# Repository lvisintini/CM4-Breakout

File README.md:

# CM4-Breakout (project discontinued)

A simple 2 layer PCB board for the Raspberry pi CM4 designed on KiCad.

##  Objectives

- Ceate a PCB board with all the CM4 pins exposed so that it can be used for prototyping as part of a breadboard.
- Learn how to layout a board in KiCad
- Learn how to design for the CM4

## Outcomes and conclusions

While it was certainly educational to attempt to design this board, I wont be finishing this project.

There are many reasons, but the main problem is that it is just not very practical:
- Most projects wont need to use everything and creating a breakout board that only uses the required features is simpler.
- Exposing some pins as anything other that the ports/jacks they are designed for is nonsensical.
- There is already an [abundance](https://github.com/geerlingguy/raspberry-pi-pcie-devices) of open-hardware projects with desing breakout boards for the CM4. There is probably no need for a new one with a narrow use case such as this one..
- Trying to fit all the traces using only 2 layers is too much of a constraint (the CM4IO uses 4)

However, this was not a waste of time:
- Learned a lot about the CM4 module
- Learned a lot about KiCad 6 (pre-release nightly versions)
- Learned a lot about PCB design in general

## Screenshot

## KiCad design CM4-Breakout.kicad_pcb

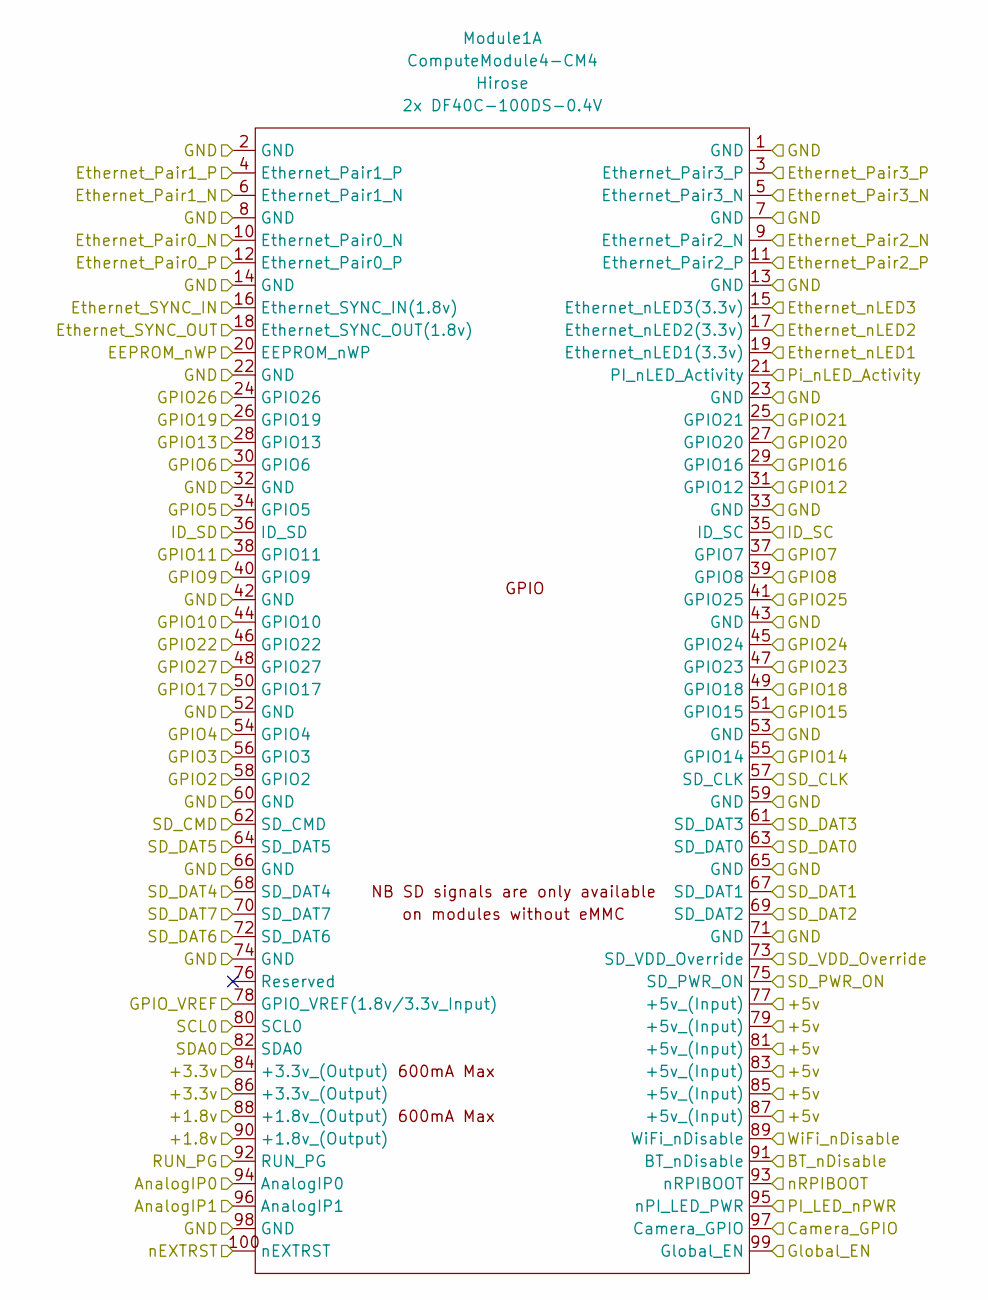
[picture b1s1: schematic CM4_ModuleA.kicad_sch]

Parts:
Module1: ComputeModule4-CM4; Raspberry-Pi-4-Compute-Module

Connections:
/+1.8v: Module1.88 (+1.8v_(Output)), Module1.90 (+1.8v_(Output)); also elsewhere on the board
/+3.3v: Module1.84 (+3.3v_(Output)), Module1.86 (+3.3v_(Output)); also elsewhere on the board
/+5v: Module1.77 (+5v_(Input)), Module1.79 (+5v_(Input)), Module1.81 (+5v_(Input)), Module1.83 (+5v_(Input)), Module1.85 (+5v_(Input)), Module1.87 (+5v_(Input)); also elsewhere on the board
/AnalogIP0: Module1.94 (AnalogIP0); also elsewhere on the board
/AnalogIP1: Module1.96 (AnalogIP1); also elsewhere on the board
/BT_nDisable: Module1.91 (BT_nDisable); also elsewhere on the board
/Camera_GPIO: Module1.97 (Camera_GPIO); also elsewhere on the board
/EEPROM_nWP: Module1.20 (EEPROM_nWP); also elsewhere on the board
/Ethernet_Pair0_N: Module1.10 (Ethernet_Pair0_N); also elsewhere on the board
/Ethernet_Pair0_P: Module1.12 (Ethernet_Pair0_P); also elsewhere on the board
/Ethernet_Pair1_N: Module1.6 (Ethernet_Pair1_N); also elsewhere on the board
/Ethernet_Pair1_P: Module1.4 (Ethernet_Pair1_P); also elsewhere on the board
/Ethernet_Pair2_N: Module1.9 (Ethernet_Pair2_N); also elsewhere on the board
/Ethernet_Pair2_P: Module1.11 (Ethernet_Pair2_P); also elsewhere on the board
/Ethernet_Pair3_N: Module1.5 (Ethernet_Pair3_N); also elsewhere on the board
/Ethernet_Pair3_P: Module1.3 (Ethernet_Pair3_P); also elsewhere on the board
/Ethernet_SYNC_IN: Module1.16 (Ethernet_SYNC_IN(1.8v)); also elsewhere on the board
/Ethernet_SYNC_OUT: Module1.18 (Ethernet_SYNC_OUT(1.8v)); also elsewhere on the board
/Ethernet_nLED1: Module1.19 (Ethernet_nLED1(3.3v)); also elsewhere on the board
/Ethernet_nLED2: Module1.17 (Ethernet_nLED2(3.3v)); also elsewhere on the board
/Ethernet_nLED3: Module1.15 (Ethernet_nLED3(3.3v)); also elsewhere on the board
/GND: Module1.1 (GND), Module1.2 (GND), Module1.7 (GND), Module1.8 (GND), Module1.13 (GND), Module1.14 (GND), Module1.22 (GND), Module1.23 (GND), Module1.32 (GND), Module1.33 (GND), Module1.42 (GND), Module1.43 (GND), Module1.52 (GND), Module1.53 (GND), Module1.59 (GND), Module1.60 (GND), Module1.65 (GND), Module1.66 (GND), Module1.71 (GND), Module1.74 (GND), Module1.98 (GND); also elsewhere on the board
/GPIO2: Module1.58 (GPIO2); also elsewhere on the board
/GPIO3: Module1.56 (GPIO3); also elsewhere on the board
/GPIO4: Module1.54 (GPIO4); also elsewhere on the board
/GPIO5: Module1.34 (GPIO5); also elsewhere on the board
/GPIO6: Module1.30 (GPIO6); also elsewhere on the board
/GPIO7: Module1.37 (GPIO7); also elsewhere on the board
/GPIO8: Module1.39 (GPIO8); also elsewhere on the board
/GPIO9: Module1.40 (GPIO9); also elsewhere on the board
/GPIO10: Module1.44 (GPIO10); also elsewhere on the board
/GPIO11: Module1.38 (GPIO11); also elsewhere on the board
/GPIO12: Module1.31 (GPIO12); also elsewhere on the board
/GPIO13: Module1.28 (GPIO13); also elsewhere on the board
/GPIO14: Module1.55 (GPIO14); also elsewhere on the board
/GPIO15: Module1.51 (GPIO15); also elsewhere on the board
/GPIO16: Module1.29 (GPIO16); also elsewhere on the board
/GPIO17: Module1.50 (GPIO17); also elsewhere on the board
/GPIO18: Module1.49 (GPIO18); also elsewhere on the board
/GPIO19: Module1.26 (GPIO19); also elsewhere on the board
/GPIO20: Module1.27 (GPIO20); also elsewhere on the board
/GPIO21: Module1.25 (GPIO21); also elsewhere on the board
/GPIO22: Module1.46 (GPIO22); also elsewhere on the board
/GPIO23: Module1.47 (GPIO23); also elsewhere on the board
/GPIO24: Module1.45 (GPIO24); also elsewhere on the board
/GPIO25: Module1.41 (GPIO25); also elsewhere on the board
/GPIO26: Module1.24 (GPIO26); also elsewhere on the board
/GPIO27: Module1.48 (GPIO27); also elsewhere on the board
/GPIO_VREF: Module1.78 (GPIO_VREF(1.8v/3.3v_Input)); also elsewhere on the board
/Global_EN: Module1.99 (Global_EN); also elsewhere on the board
/ID_SC: Module1.35 (ID_SC); also elsewhere on the board
/ID_SD: Module1.36 (ID_SD); also elsewhere on the board
/PI_LED_nPWR: Module1.95 (nPI_LED_PWR); also elsewhere on the board
/Pi_nLED_Activity: Module1.21 (PI_nLED_Activity); also elsewhere on the board
/RUN_PG: Module1.92 (RUN_PG); also elsewhere on the board
/SCL0: Module1.80 (SCL0); also elsewhere on the board
/SDA0: Module1.82 (SDA0); also elsewhere on the board
/SD_CLK: Module1.57 (SD_CLK); also elsewhere on the board
/SD_CMD: Module1.62 (SD_CMD); also elsewhere on the board
/SD_DAT0: Module1.63 (SD_DAT0); also elsewhere on the board
/SD_DAT1: Module1.67 (SD_DAT1); also elsewhere on the board
/SD_DAT2: Module1.69 (SD_DAT2); also elsewhere on the board
/SD_DAT3: Module1.61 (SD_DAT3); also elsewhere on the board
/SD_DAT4: Module1.68 (SD_DAT4); also elsewhere on the board
/SD_DAT5: Module1.64 (SD_DAT5); also elsewhere on the board
/SD_DAT6: Module1.72 (SD_DAT6); also elsewhere on the board
/SD_DAT7: Module1.70 (SD_DAT7); also elsewhere on the board
/SD_PWR_ON: Module1.75 (SD_PWR_ON); also elsewhere on the board
/SD_VDD_Override: Module1.73 (SD_VDD_Override); also elsewhere on the board
/WiFi_nDisable: Module1.89 (WiFi_nDisable); also elsewhere on the board
/nEXTRST: Module1.100 (nEXTRST); also elsewhere on the board
/nRPIBOOT: Module1.93 (nRPIBOOT); also elsewhere on the board
no_connect_143: Module1.76 (Reserved)

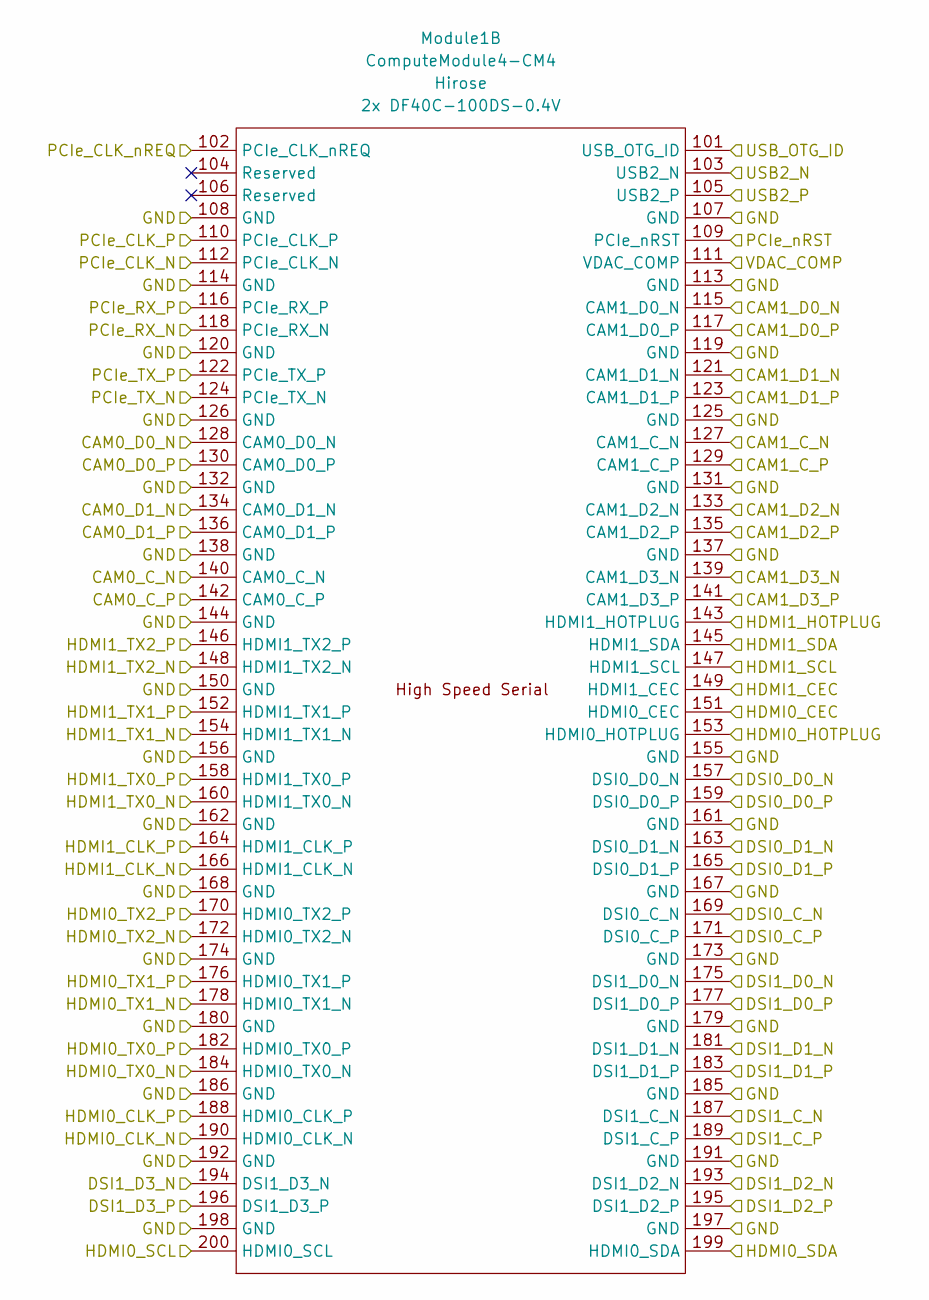
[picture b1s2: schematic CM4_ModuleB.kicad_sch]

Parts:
Module1: ComputeModule4-CM4; Raspberry-Pi-4-Compute-Module

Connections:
/CAM0_C_N: Module1.140 (CAM0_C_N); also elsewhere on the board
/CAM0_C_P: Module1.142 (CAM0_C_P); also elsewhere on the board
/CAM0_D0_N: Module1.128 (CAM0_D0_N); also elsewhere on the board
/CAM0_D0_P: Module1.130 (CAM0_D0_P); also elsewhere on the board
/CAM0_D1_N: Module1.134 (CAM0_D1_N); also elsewhere on the board
/CAM0_D1_P: Module1.136 (CAM0_D1_P); also elsewhere on the board
/CAM1_C_N: Module1.127 (CAM1_C_N); also elsewhere on the board
/CAM1_C_P: Module1.129 (CAM1_C_P); also elsewhere on the board
/CAM1_D0_N: Module1.115 (CAM1_D0_N); also elsewhere on the board
/CAM1_D0_P: Module1.117 (CAM1_D0_P); also elsewhere on the board
/CAM1_D1_N: Module1.121 (CAM1_D1_N); also elsewhere on the board
/CAM1_D1_P: Module1.123 (CAM1_D1_P); also elsewhere on the board
/CAM1_D2_N: Module1.133 (CAM1_D2_N); also elsewhere on the board
/CAM1_D2_P: Module1.135 (CAM1_D2_P); also elsewhere on the board
/CAM1_D3_N: Module1.139 (CAM1_D3_N); also elsewhere on the board
/CAM1_D3_P: Module1.141 (CAM1_D3_P); also elsewhere on the board
/DSI0_C_N: Module1.169 (DSI0_C_N); also elsewhere on the board
/DSI0_C_P: Module1.171 (DSI0_C_P); also elsewhere on the board
/DSI0_D0_N: Module1.157 (DSI0_D0_N); also elsewhere on the board
/DSI0_D0_P: Module1.159 (DSI0_D0_P); also elsewhere on the board
/DSI0_D1_N: Module1.163 (DSI0_D1_N); also elsewhere on the board
/DSI0_D1_P: Module1.165 (DSI0_D1_P); also elsewhere on the board
/DSI1_C_N: Module1.187 (DSI1_C_N); also elsewhere on the board
/DSI1_C_P: Module1.189 (DSI1_C_P); also elsewhere on the board
/DSI1_D0_N: Module1.175 (DSI1_D0_N); also elsewhere on the board
/DSI1_D0_P: Module1.177 (DSI1_D0_P); also elsewhere on the board
/DSI1_D1_N: Module1.181 (DSI1_D1_N); also elsewhere on the board
/DSI1_D1_P: Module1.183 (DSI1_D1_P); also elsewhere on the board
/DSI1_D2_N: Module1.193 (DSI1_D2_N); also elsewhere on the board
/DSI1_D2_P: Module1.195 (DSI1_D2_P); also elsewhere on the board
/DSI1_D3_N: Module1.194 (DSI1_D3_N); also elsewhere on the board
/DSI1_D3_P: Module1.196 (DSI1_D3_P); also elsewhere on the board
/GND: Module1.107 (GND), Module1.108 (GND), Module1.113 (GND), Module1.114 (GND), Module1.119 (GND), Module1.120 (GND), Module1.125 (GND), Module1.126 (GND), Module1.131 (GND), Module1.132 (GND), Module1.137 (GND), Module1.138 (GND), Module1.144 (GND), Module1.150 (GND), Module1.155 (GND), Module1.156 (GND), Module1.161 (GND), Module1.162 (GND), Module1.167 (GND), Module1.168 (GND), Module1.173 (GND), Module1.174 (GND), Module1.179 (GND), Module1.180 (GND), Module1.185 (GND), Module1.186 (GND), Module1.191 (GND), Module1.192 (GND), Module1.197 (GND), Module1.198 (GND); also elsewhere on the board
/HDMI0_CEC: Module1.151 (HDMI0_CEC); also elsewhere on the board
/HDMI0_CLK_N: Module1.190 (HDMI0_CLK_N); also elsewhere on the board
/HDMI0_CLK_P: Module1.188 (HDMI0_CLK_P); also elsewhere on the board
/HDMI0_HOTPLUG: Module1.153 (HDMI0_HOTPLUG); also elsewhere on the board
/HDMI0_SCL: Module1.200 (HDMI0_SCL); also elsewhere on the board
/HDMI0_SDA: Module1.199 (HDMI0_SDA); also elsewhere on the board
/HDMI0_TX0_N: Module1.184 (HDMI0_TX0_N); also elsewhere on the board
/HDMI0_TX0_P: Module1.182 (HDMI0_TX0_P); also elsewhere on the board
/HDMI0_TX1_N: Module1.178 (HDMI0_TX1_N); also elsewhere on the board
/HDMI0_TX1_P: Module1.176 (HDMI0_TX1_P); also elsewhere on the board
/HDMI0_TX2_N: Module1.172 (HDMI0_TX2_N); also elsewhere on the board
/HDMI0_TX2_P: Module1.170 (HDMI0_TX2_P); also elsewhere on the board
/HDMI1_CEC: Module1.149 (HDMI1_CEC); also elsewhere on the board
/HDMI1_CLK_N: Module1.166 (HDMI1_CLK_N); also elsewhere on the board
/HDMI1_CLK_P: Module1.164 (HDMI1_CLK_P); also elsewhere on the board
/HDMI1_HOTPLUG: Module1.143 (HDMI1_HOTPLUG); also elsewhere on the board
/HDMI1_SCL: Module1.147 (HDMI1_SCL); also elsewhere on the board
/HDMI1_SDA: Module1.145 (HDMI1_SDA); also elsewhere on the board
/HDMI1_TX0_N: Module1.160 (HDMI1_TX0_N); also elsewhere on the board
/HDMI1_TX0_P: Module1.158 (HDMI1_TX0_P); also elsewhere on the board
/HDMI1_TX1_N: Module1.154 (HDMI1_TX1_N); also elsewhere on the board
/HDMI1_TX1_P: Module1.152 (HDMI1_TX1_P); also elsewhere on the board
/HDMI1_TX2_N: Module1.148 (HDMI1_TX2_N); also elsewhere on the board
/HDMI1_TX2_P: Module1.146 (HDMI1_TX2_P); also elsewhere on the board
/PCIe_CLK_N: Module1.112 (PCIe_CLK_N); also elsewhere on the board
/PCIe_CLK_P: Module1.110 (PCIe_CLK_P); also elsewhere on the board
/PCIe_CLK_nREQ: Module1.102 (PCIe_CLK_nREQ); also elsewhere on the board
/PCIe_RX_N: Module1.118 (PCIe_RX_N); also elsewhere on the board
/PCIe_RX_P: Module1.116 (PCIe_RX_P); also elsewhere on the board
/PCIe_TX_N: Module1.124 (PCIe_TX_N); also elsewhere on the board
/PCIe_TX_P: Module1.122 (PCIe_TX_P); also elsewhere on the board
/PCIe_nRST: Module1.109 (PCIe_nRST); also elsewhere on the board
/USB2_N: Module1.103 (USB2_N); also elsewhere on the board
/USB2_P: Module1.105 (USB2_P); also elsewhere on the board
/USB_OTG_ID: Module1.101 (USB_OTG_ID); also elsewhere on the board
/VDAC_COMP: Module1.111 (VDAC_COMP); also elsewhere on the board
no_connect_141: Module1.104 (Reserved)
no_connect_142: Module1.106 (Reserved)

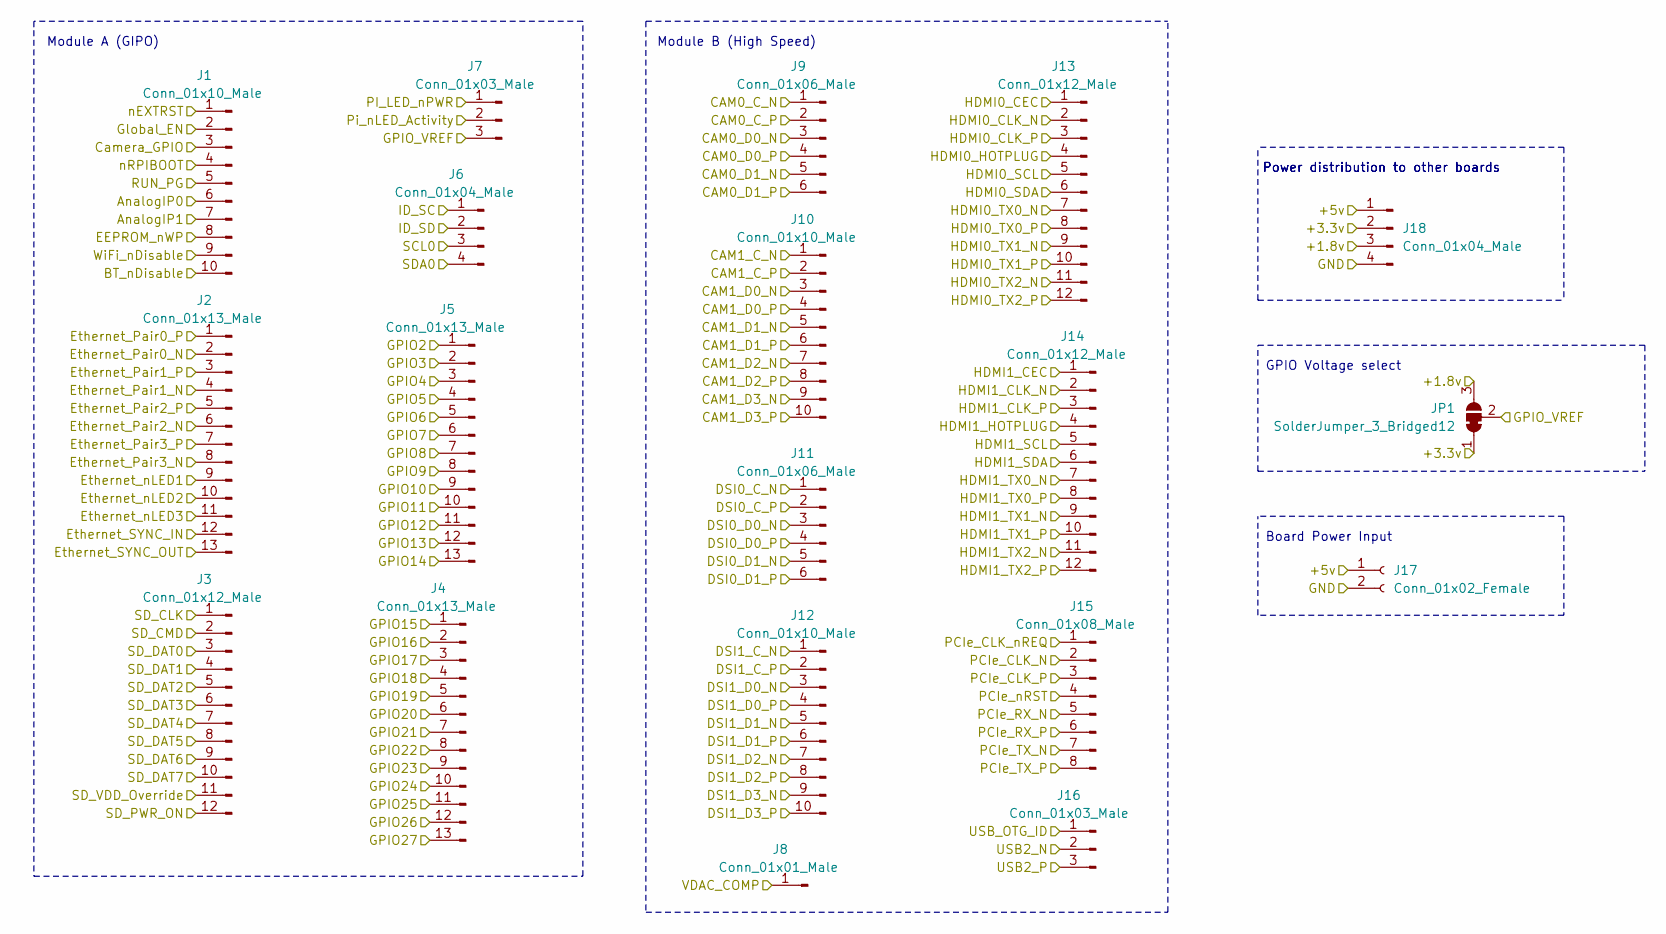
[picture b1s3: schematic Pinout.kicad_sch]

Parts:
J1, J10, J12: Conn_01x10_Male; PinHeader_1x10_P2.54mm_Vertical
J2, J4, J5: Conn_01x13_Male; PinHeader_1x13_P2.54mm_Vertical
J3, J13, J14: Conn_01x12_Male; PinHeader_1x12_P2.54mm_Vertical
J6, J18: Conn_01x04_Male; PinHeader_1x04_P2.54mm_Vertical
J7, J16: Conn_01x03_Male; PinHeader_1x03_P2.54mm_Vertical
J8: Conn_01x01_Male; PinHeader_1x01_P2.54mm_Vertical
J9, J11: Conn_01x06_Male; PinHeader_1x06_P2.54mm_Vertical
J15: Conn_01x08_Male; PinHeader_1x08_P2.54mm_Vertical
J17: Conn_01x02_Female; PinHeader_1x02_P2.54mm_Vertical
JP1: SolderJumper_3_Bridged12; SolderJumper-3_P1.3mm_Bridged12_RoundedPad1.0x1.5mm

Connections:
/+1.8v: J18.3, JP1.3 (B); also elsewhere on the board
/+3.3v: J18.2, JP1.1 (A); also elsewhere on the board
/+5v: J17.1, J18.1; also elsewhere on the board
/AnalogIP0: J1.6; also elsewhere on the board
/AnalogIP1: J1.7; also elsewhere on the board
/BT_nDisable: J1.10; also elsewhere on the board
/CAM0_C_N: J9.1; also elsewhere on the board
/CAM0_C_P: J9.2; also elsewhere on the board
/CAM0_D0_N: J9.3; also elsewhere on the board
/CAM0_D0_P: J9.4; also elsewhere on the board
/CAM0_D1_N: J9.5; also elsewhere on the board
/CAM0_D1_P: J9.6; also elsewhere on the board
/CAM1_C_N: J10.1; also elsewhere on the board
/CAM1_C_P: J10.2; also elsewhere on the board
/CAM1_D0_N: J10.3; also elsewhere on the board
/CAM1_D0_P: J10.4; also elsewhere on the board
/CAM1_D1_N: J10.5; also elsewhere on the board
/CAM1_D1_P: J10.6; also elsewhere on the board
/CAM1_D2_N: J10.7; also elsewhere on the board
/CAM1_D2_P: J10.8; also elsewhere on the board
/CAM1_D3_N: J10.9; also elsewhere on the board
/CAM1_D3_P: J10.10; also elsewhere on the board
/Camera_GPIO: J1.3; also elsewhere on the board
/DSI0_C_N: J11.1; also elsewhere on the board
/DSI0_C_P: J11.2; also elsewhere on the board
/DSI0_D0_N: J11.3; also elsewhere on the board
/DSI0_D0_P: J11.4; also elsewhere on the board
/DSI0_D1_N: J11.5; also elsewhere on the board
/DSI0_D1_P: J11.6; also elsewhere on the board
/DSI1_C_N: J12.1; also elsewhere on the board
/DSI1_C_P: J12.2; also elsewhere on the board
/DSI1_D0_N: J12.3; also elsewhere on the board
/DSI1_D0_P: J12.4; also elsewhere on the board
/DSI1_D1_N: J12.5; also elsewhere on the board
/DSI1_D1_P: J12.6; also elsewhere on the board
/DSI1_D2_N: J12.7; also elsewhere on the board
/DSI1_D2_P: J12.8; also elsewhere on the board
/DSI1_D3_N: J12.9; also elsewhere on the board
/DSI1_D3_P: J12.10; also elsewhere on the board
/EEPROM_nWP: J1.8; also elsewhere on the board
/Ethernet_Pair0_N: J2.2; also elsewhere on the board
/Ethernet_Pair0_P: J2.1; also elsewhere on the board
/Ethernet_Pair1_N: J2.4; also elsewhere on the board
/Ethernet_Pair1_P: J2.3; also elsewhere on the board
/Ethernet_Pair2_N: J2.6; also elsewhere on the board
/Ethernet_Pair2_P: J2.5; also elsewhere on the board
/Ethernet_Pair3_N: J2.8; also elsewhere on the board
/Ethernet_Pair3_P: J2.7; also elsewhere on the board
/Ethernet_SYNC_IN: J2.12; also elsewhere on the board
/Ethernet_SYNC_OUT: J2.13; also elsewhere on the board
/Ethernet_nLED1: J2.9; also elsewhere on the board
/Ethernet_nLED2: J2.10; also elsewhere on the board
/Ethernet_nLED3: J2.11; also elsewhere on the board
/GND: J17.2, J18.4; also elsewhere on the board
/GPIO2: J5.1; also elsewhere on the board
/GPIO3: J5.2; also elsewhere on the board
/GPIO4: J5.3; also elsewhere on the board
/GPIO5: J5.4; also elsewhere on the board
/GPIO6: J5.5; also elsewhere on the board
/GPIO7: J5.6; also elsewhere on the board
/GPIO8: J5.7; also elsewhere on the board
/GPIO9: J5.8; also elsewhere on the board
/GPIO10: J5.9; also elsewhere on the board
/GPIO11: J5.10; also elsewhere on the board
/GPIO12: J5.11; also elsewhere on the board
/GPIO13: J5.12; also elsewhere on the board
/GPIO14: J5.13; also elsewhere on the board
/GPIO15: J4.1; also elsewhere on the board
/GPIO16: J4.2; also elsewhere on the board
/GPIO17: J4.3; also elsewhere on the board
/GPIO18: J4.4; also elsewhere on the board
/GPIO19: J4.5; also elsewhere on the board
/GPIO20: J4.6; also elsewhere on the board
/GPIO21: J4.7; also elsewhere on the board
/GPIO22: J4.8; also elsewhere on the board
/GPIO23: J4.9; also elsewhere on the board
/GPIO24: J4.10; also elsewhere on the board
/GPIO25: J4.11; also elsewhere on the board
/GPIO26: J4.12; also elsewhere on the board
/GPIO27: J4.13; also elsewhere on the board
/GPIO_VREF: J7.3, JP1.2 (C); also elsewhere on the board
/Global_EN: J1.2; also elsewhere on the board
/HDMI0_CEC: J13.1; also elsewhere on the board
/HDMI0_CLK_N: J13.2; also elsewhere on the board
/HDMI0_CLK_P: J13.3; also elsewhere on the board
/HDMI0_HOTPLUG: J13.4; also elsewhere on the board
/HDMI0_SCL: J13.5; also elsewhere on the board
/HDMI0_SDA: J13.6; also elsewhere on the board
/HDMI0_TX0_N: J13.7; also elsewhere on the board
/HDMI0_TX0_P: J13.8; also elsewhere on the board
/HDMI0_TX1_N: J13.9; also elsewhere on the board
/HDMI0_TX1_P: J13.10; also elsewhere on the board
/HDMI0_TX2_N: J13.11; also elsewhere on the board
/HDMI0_TX2_P: J13.12; also elsewhere on the board
/HDMI1_CEC: J14.1; also elsewhere on the board
/HDMI1_CLK_N: J14.2; also elsewhere on the board
/HDMI1_CLK_P: J14.3; also elsewhere on the board
/HDMI1_HOTPLUG: J14.4; also elsewhere on the board
/HDMI1_SCL: J14.5; also elsewhere on the board
/HDMI1_SDA: J14.6; also elsewhere on the board
/HDMI1_TX0_N: J14.7; also elsewhere on the board
/HDMI1_TX0_P: J14.8; also elsewhere on the board
/HDMI1_TX1_N: J14.9; also elsewhere on the board
/HDMI1_TX1_P: J14.10; also elsewhere on the board
/HDMI1_TX2_N: J14.11; also elsewhere on the board
/HDMI1_TX2_P: J14.12; also elsewhere on the board
/ID_SC: J6.1; also elsewhere on the board
/ID_SD: J6.2; also elsewhere on the board
/PCIe_CLK_N: J15.2; also elsewhere on the board
/PCIe_CLK_P: J15.3; also elsewhere on the board
/PCIe_CLK_nREQ: J15.1; also elsewhere on the board
/PCIe_RX_N: J15.5; also elsewhere on the board
/PCIe_RX_P: J15.6; also elsewhere on the board
/PCIe_TX_N: J15.7; also elsewhere on the board
/PCIe_TX_P: J15.8; also elsewhere on the board
/PCIe_nRST: J15.4; also elsewhere on the board
/PI_LED_nPWR: J7.1; also elsewhere on the board
/Pi_nLED_Activity: J7.2; also elsewhere on the board
/RUN_PG: J1.5; also elsewhere on the board
/SCL0: J6.3; also elsewhere on the board
/SDA0: J6.4; also elsewhere on the board
/SD_CLK: J3.1; also elsewhere on the board
/SD_CMD: J3.2; also elsewhere on the board
/SD_DAT0: J3.3; also elsewhere on the board
/SD_DAT1: J3.4; also elsewhere on the board
/SD_DAT2: J3.5; also elsewhere on the board
/SD_DAT3: J3.6; also elsewhere on the board
/SD_DAT4: J3.7; also elsewhere on the board
/SD_DAT5: J3.8; also elsewhere on the board
/SD_DAT6: J3.9; also elsewhere on the board
/SD_DAT7: J3.10; also elsewhere on the board
/SD_PWR_ON: J3.12; also elsewhere on the board
/SD_VDD_Override: J3.11; also elsewhere on the board
/USB2_N: J16.2; also elsewhere on the board
/USB2_P: J16.3; also elsewhere on the board
/USB_OTG_ID: J16.1; also elsewhere on the board
/VDAC_COMP: J8.1; also elsewhere on the board
/WiFi_nDisable: J1.9; also elsewhere on the board
/nEXTRST: J1.1; also elsewhere on the board
/nRPIBOOT: J1.4; also elsewhere on the board

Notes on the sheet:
Module A (GIPO)
Module B (High Speed)
Board Power Input
GPIO Voltage select
Power distribution to other boards

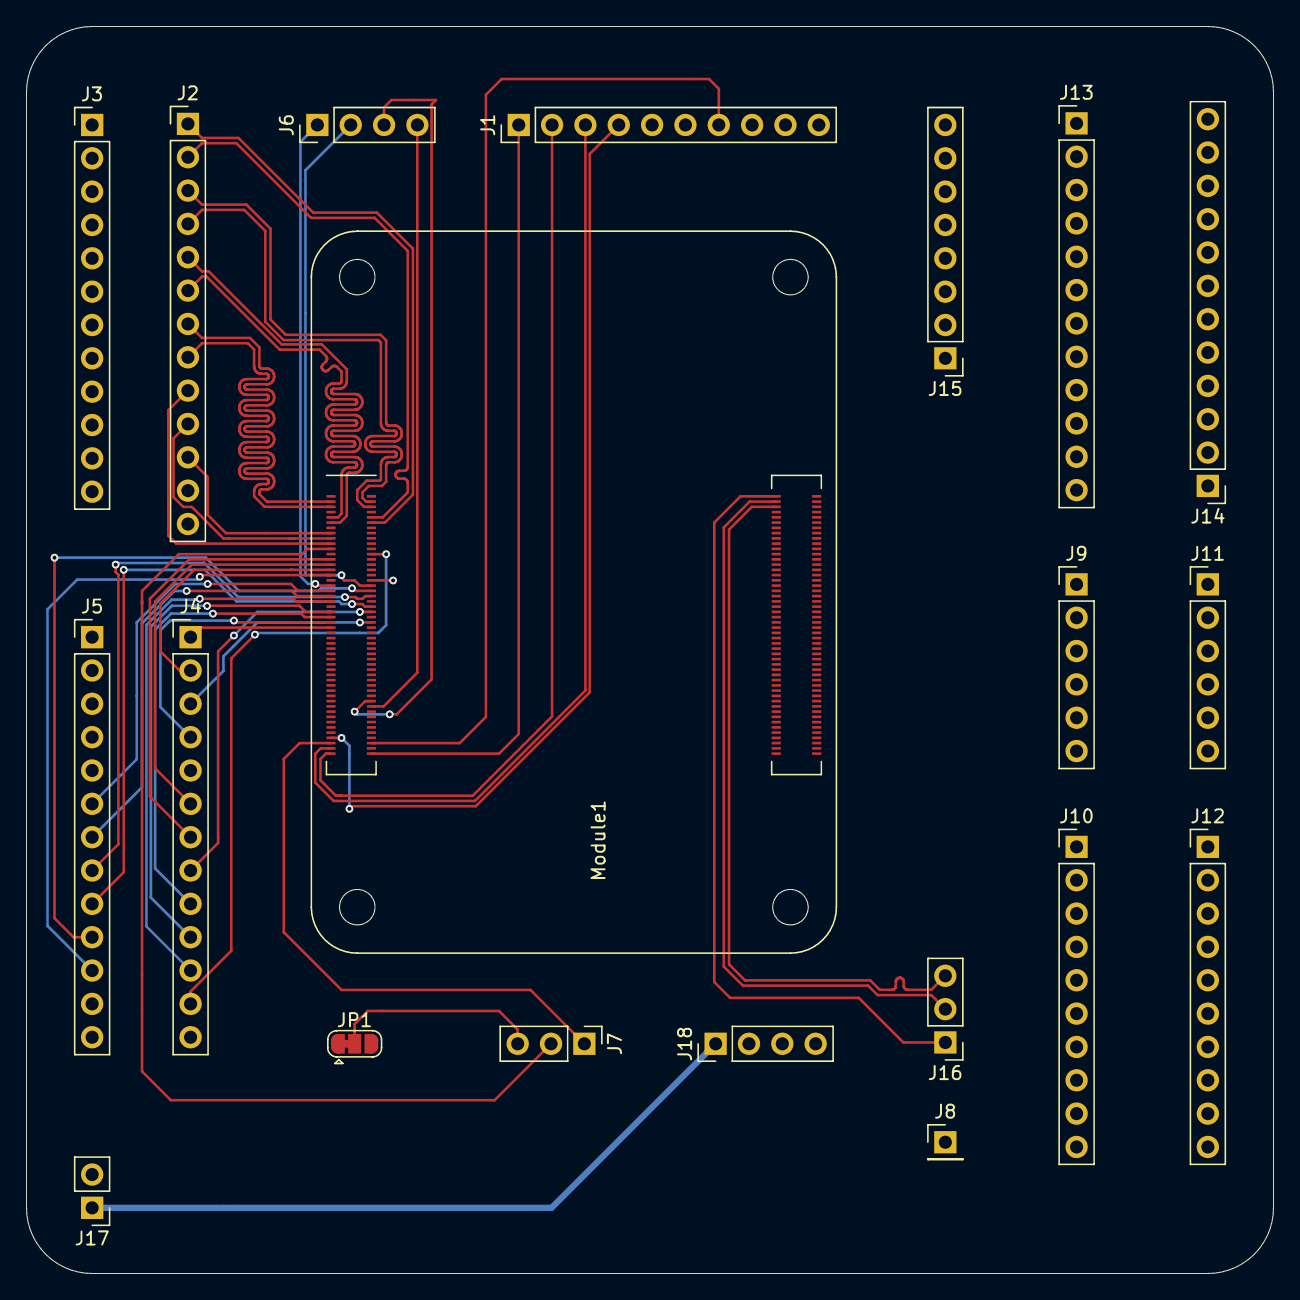
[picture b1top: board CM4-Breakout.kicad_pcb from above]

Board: 2 copper layers, 95.0 x 95.0 mm, 20 parts (0 on the bottom side), 140 nets.

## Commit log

2020-11-23 Project start
2020-12-02 Some work was done
2020-12-03 PCB ready to trace
2020-12-10 Add CM4IO as local lib
2020-12-12 Some updates to the pinout
2020-12-20 Final
